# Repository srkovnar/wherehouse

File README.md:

# Wherehouse

Author(s): Sam Kovnar, Sam Hild, Alex Burrowes, Will Oberley

## About this repository

This is the main repository for Team 23, Purdue ECE Senior Design 49022, Spring 2023.

- Subsystem code will be kept in separate folders with the name of the subsystem.
- System code will be found in the folder marked "System".

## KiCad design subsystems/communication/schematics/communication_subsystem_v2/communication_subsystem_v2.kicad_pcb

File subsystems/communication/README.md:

# Wherehouse: Communication Subsystem

Author(s): Sam Kovnar (Github: srkovnar)

With additional credit to: 
- me-no-dev
- jdunmire

## Table of Contents

1. [TL;DR for TAs and Instructors](#tldr)
2. [About this folder](#about)
3. [Hardware Dependencies](#hardware)
4. [Software Dependencies](#software)
    1. [General](#sw_general)
    2. [ESP8266 Core for Arduino IDE](#esp8266core)
    3. [Additional Firmware Libraries](#fw_libraries)
    4. [KiCad Libraries](#kicad_libraries)
5. [ESP8266 Firmware](#esp_firmware)
    1. [Testing Phase 1](#esp_fw_t1)
    2. [Testing Phase 2](#esp_fw_t2)
    3. [Release Firmware](#esp_fw_release)
6. [Schematics](#schematics)
7. [Documentation](#documentation)

## TL;DR for TAs and Instructors 

The code used for the ESP8266 in the Midterm Demo is at 
`subsystems/communication/esp8266_firmware/esp8266_release/esp8266_release.ino`.
The files contained in `subsystems/communication/esp8266_test_code`
were used for testing and are not being used in the design at this
time. They are being kept solely as documentation.

## About this folder 

This folder (`wherehouse/subsystems/communication`) contains the code
used to test the Communications subsystem of the Wherehouse, Team 23's
Spring 2023 ECE senior design project.

The Communication subsystem is responsible for interactions between the
STM32F0 microcontroller and ESP8266 Wi-Fi module.

## Hardware Dependencies 

The code for ESP8266 devices has been tested on Ai-Thinker's ESP8266 ESP-01 modules.

For flashing and testing the ESP8266 ESP-01 modules, I recommend using
a ESP-01 USB adapter. You can find these from multiple different
vendors. I found mine on eBay.

## Software Dependencies 

### General 

Operating System: Ubuntu 22.04 LTS
- Code functionality on other operating systems can be neither confirmed nor denied

Arduino IDE *(version 2.0.0 or later)*
- This version has been tested on Arduino v2.0.3
- Certain libraries do not work on versions earlier than v2.0.0 for Linux

KiCad *(version 6.0)*
- Certain libraries used for this project are for older versions of
KiCad, but they work fine on more recent versions as well.

### ESP8266 Core for Arduino IDE 

ESP8266 Core for Arduino *(version 3.1.1)*
- ESP8266WiFi.h
- ESP8266HTTPClient.h
- ESP8266WiFiMulti.h

Multiple libraries used in the code contained in this project utilize the ESP8266
Core for Arduino IDE. You must make sure that it is installed.

1.  Open Arduino IDE
2.  Navigate to File > Preferences
3.  Find the textbox labeled "Additional Board Manager URLs"
4.  Insert the following link into the box: http://arduino.esp8266.com/stable/package_esp8266com_index.json, then click "OK".
    - You can have multiple URLs in the box. Just separate them with commas.
5.  Navigate to "Boards Manager"
6.  Search for "esp8266"
7.  Install the board labeled "esp8266 by ESP8266 Community"

### Additional Arduino IDE Libraries 

ESPAsyncWebServer.h (https://github.com/me-no-dev/ESPAsyncWebServer)
- Used by ESP8266 firmware and test code

ESPAsyncTCP.h (https://github.com/me-no-dev/ESPAsyncTCP)
- Required for ESPAsyncWebServer.h to work

To install an Arduino library:
1. Download the library from Github.
    1. Open the Github link to the library in a web browser
    2. Click on the button that says "<> Code". This will bring up a menu.
    3. In the menu that appears, click on "Download ZIP". This will download a .zip folder containing all of the files needed for the library to work.
    4. Keep track of where this .zip file is. It will probably be in your "Downloads" folder.
2. Open Arduino IDE
3. Add the library to your Arduino libraries.
    1. In the toolbar at the top of the Arduino IDE window, click "Sketch" to bring up a drop-down menu.
    2. Hover over "Include Library", then click on "Add .ZIP Library...". A window will appear showing your files.
    3. In the window that just appeared, find the .zip file that you downloaded in step 1. It is most likely in your downloads folder with a name that matches the name of the library (For example, the .zip for ESPAsyncWebServer.h is called `ESPAsyncWebServer-Master.zip`).
    4. Click on the .zip file, then click the "Open" button. This will put the library in your Arduino libraries folder (usually `~/Arduino/libraries` or something similar).
    5. You can delete the .zip file now. You don't need it anymore.
4. The library is now available for you to use, and can be targeted by adding `#include <LIBRARY_NAME.h>` to your code, where "LIBRARY_NAME" is replaced with the name of your library, for example, ESPAsyncWebServer.h.

### KiCad Libraries 

kicad-ESP8266 (https://github.com/jdunmire/kicad-ESP8266)
- Contains schematic and PCB footprints for most commonly used ESP8266 modules, including the ESP-01 which is being used in this project.

To install a KiCad library:
1. Download files from the Github link listed above
2. Open KiCad
3. In the toolbar, go to "Preferences", then click on "Manage Symbol Libraries". A window will appear.
4. In the window that just appeared, click on "Global Libraries" near the top.
5. Click on the Folder icon near the bottom.
6. In the file browser that appears, find the file `kicad-ESP8266/ESP8266.lib`. Click on it, then click "Open".
7. Name it "ESP8266", then click "OK".
8. Repeat steps 3 through 7, but go to "Manage Footprint Libraries" instead of "Manage Symbol Libraries".

## Firmware 

All code for the ESP8266 is written in Arduino format (.ino).
ESP8266 code files begin with 'esp8266_' followed by the name of the
specific project.

Due to the nature of the Arduino IDE, all code files must be kept in
their own folder which shares the project name with the '.ino' file.

### ESP8266 Testing Stage 1: Communications 

**esp8266_ap_test**: Connection test for ESP8266 acting as Access Point

**esp8266_sta_test**: Connection test for ESP8266 acting as Station

The above two code files are a simple test of the ESP8266 WiFi libraries.
The Access Point device should produce serial output that a WiFi access point
was started successfully. Once the Access Point is created, the Station device
should be able to connect and display connection status over Serial lines.

This code was last tested 2023-02-14.

**esp8266_ap_http_test**: HTTP transfer test for ESP8266 acting as Access Point

**esp8266_sta_http_test**: HTTP transfer test for ESP8266 acting as Station

The above two code files are based on a tutorial by RandomNerdTutorials
at https://randomnerdtutorials.com/esp8266-nodemcu-client-server-wi-fi/.
Each should be loaded onto an ESP8266. When both ESP devices are active
(i.e. powered on and running in operation mode), the Station device should
be able to receive data from the Access Point device by requesting from
the /data URL.

This code was last tested 2023-02-16.

### ESP8266 Testing Stage 2: Functionality 

**esp8266_serial_test**: Code for testing Serial UART communication to and from the ESP8266
- Includes a handler for interpreting UART commands
- Serial commands can be sent from the host computer to the ESP8266 via
the Arduino IDE serial monitor
  - Baud rate: 115200
  - In this way, the computer can mimic the behavior of the STM32 which will be
    managing data in the final project
    
**esp8266_sta_router_test**: Test interactions between ESP8266 station and web server via router

### Release Firmware 

**esp8266_release**: Firmware to be used on device
- *This is the code being used in the midterm demo*!

## Schematics 

Schematics for the Communication subsystem are stored in the 
`wherehouse/subsystems/communication/Schematics` directory.

## Documentation 

This folder contains:
- Activity Diagram (`communication_activity_diagram.pdf`), which shows interactions between
microcontroller, wi-fi module, and the web server.
- Block Diagram (`communication_block_diagram.pdf`), which shows the signal connections between
the microcontroller and the wi-fi module.
- PCB Design Review Submission (`communication_pcb_design_review_submission_1.pdf`), which was submitted for the subsystem PCB design review. The schematic used was Version 2.

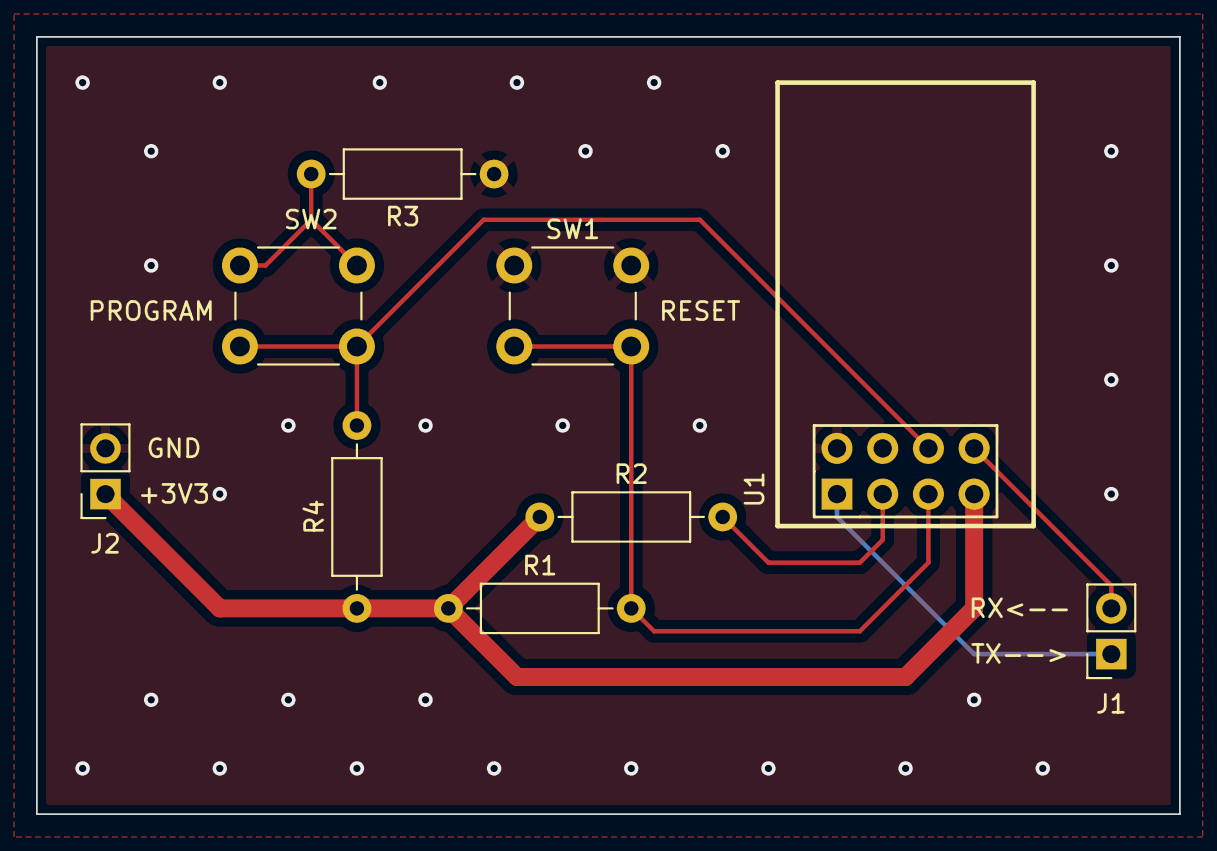
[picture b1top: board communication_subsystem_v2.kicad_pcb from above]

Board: 2 copper layers, 63.5 x 43.2 mm, 9 parts (0 on the bottom side), 8 nets.

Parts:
J1: STM32_placeholder; PinSocket_1x02_P2.54mm_Vertical
J2: power_port; PinSocket_1x02_P2.54mm_Vertical
R1, R2, R4: 10k; R_Axial_DIN0207_L6.3mm_D2.5mm_P10.16mm_Horizontal
R3: 470; R_Axial_DIN0207_L6.3mm_D2.5mm_P10.16mm_Horizontal
SW1: RESET; SW_PUSH_6mm_H5mm
SW2: PROGRAM; SW_PUSH_6mm_H5mm
U1: ESP-01v090; ESP-01

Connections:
+3V3: J2.1, R1.1, R2.1, R4.1, U1.7 (VCC)
/EN: R2.2, U1.3 (CH_PD)
/GPIO0: R4.2, SW2.1, U1.6 (GPIO0)
/esp8266_rx: J1.2, U1.8 (URXD)
/esp8266_tx: J1.1, U1.1 (UTXD)
/rst: R1.2, SW1.2, U1.5 (RST)
GND: J2.2, R3.1, SW1.1, U1.2 (GND)
unnamed: R3.2, SW2.2

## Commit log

2023-02-21 Creating README
2023-02-21 Creating system folder
2023-02-21 Adding subsystem and system readmes
2023-02-21 Migrating communication files
2023-02-21 Readme changes
2023-02-21 Moved code into its own folder
2023-02-23 Added more command support
2023-02-23 Added Display Drivers
2023-02-23 Updated firmware with new table parameters
2023-02-23 Creating release firmware
2023-02-26 Updating release firmware
2023-02-26 Moving files around for fun
2023-02-28 reorganizing folders
2023-02-28 schematics->Schematics
2023-02-28 Deleted backups from v2
2023-02-28 renaming
2023-02-28 lowercase
2023-02-28 Testing table of contents
2023-02-28 Updating table of contents
2023-02-28 Fixing subpoints ToC
2023-02-28 Bullet point tweak
2023-02-28 Renaming and added Schematic v2
2023-02-28 More renaming
2023-02-28 Adding kicad library info
2023-03-02 +Arduino library installation instructions
2023-03-02 +Credit, other changes
2023-03-21 Added EEPROM and Miniserver functionality
2023-03-23 Adding stm32 comms workspace
2023-03-28 Sensor
2023-04-02 System swap
2023-04-02 Fix 1 for release code
2023-04-02 Idk I'm just adding these files
2023-04-02 Removing dummmy html
2023-04-03 Fixed DCON and PING, improved flags
2023-04-04 integrated sensors and dispaly
2023-04-06 Idk y these metadata files keep changing
2023-04-09 Comm code merged into main code
2023-04-09 metadata
2023-04-09 idk what these do but sure
2023-04-13 HAHAHAHAHAHA
2023-04-13 Header files are messy
2023-04-13 Metadata?
2023-04-20 Buttons working ish
